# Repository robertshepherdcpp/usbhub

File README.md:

# house of wires
my fifth project for fallout!

**what is it?**
- the house of wires is a project to help remove the mess of wires! having a hub that usbs connect to creating a more organized layout
- the project is made to resemble a model house in which wires are connected and the project handles the rest (power etc.)
- the available usb options: 1 usb c power output, 3 usb a outputs (e.g. for charging your phone, charging your watch and anything else that needs charging)
- and then there is one usb input which spilts off into the other usb ports.

**how to use it?**
- print off the case and pcb (and purchase all items from the BOM)
- then to put the case on put the top half the case on the pcb (you know its the top if it has a door) and the base on the bottom, then using the 4M screws screw through. the parts of the screws pointing out the back
act as the base of the project!.
- then simply plug in a usb c port into the project (at the top)
- then connect the other usbs u need!
- just use these usbs as normal!

**how it works**
- the brain of this project is the SL2.1S, which splits the input usb into 5 channels!
- i didnt write any additional firmware for this project, that was all that was needed!

**how i made the project**
- made using kicad (for the pcb) and fusion (for the CAD design)
- using the fallout tutorial (as shown below) as a guide.

**my inspiration for the project/the why**
- i find that my desk is always messy with various wires, and i thought it would be cool to have a way to organise these (and do it in a fun way aswell!)
- i saw that there was a tutorial for a usb hub on [fallout](https://fallout.hackclub.com/docs/guided-projects/usb-hub), so i decided to give it a go (helping to improve my hardware skills!)

**screenshots:**
the schematic:

the pcb layout:

3d model:

the cad:

zine:

**the BOM**

total cost: $17.02 (not including shipping from digitkey and lcsc)

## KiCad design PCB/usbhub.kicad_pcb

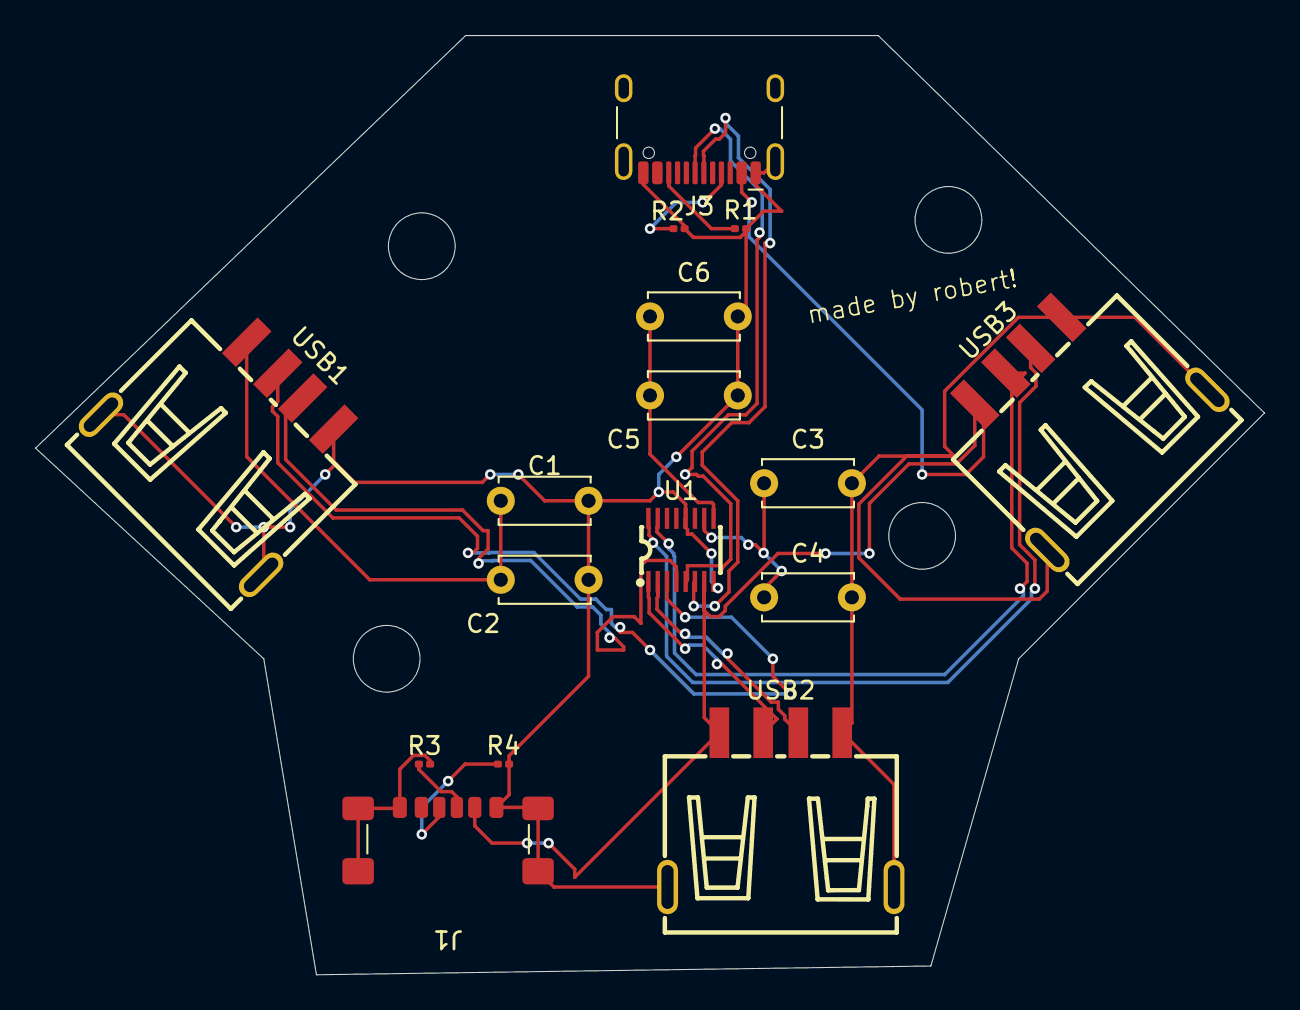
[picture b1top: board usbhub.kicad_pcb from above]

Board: 2 copper layers, 70.0 x 53.5 mm, 16 parts (0 on the bottom side), 16 nets.

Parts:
C1, C2: 1uf; C_Disc_D5.0mm_W2.5mm_P5.00mm
C3, C5: 1uF; C_Disc_D5.0mm_W2.5mm_P5.00mm
C4, C6: 100nF; C_Disc_D5.0mm_W2.5mm_P5.00mm
J1: USB_C_Receptacle_PowerOnly_6P; USB_C_Receptacle_GCT_USB4135-GF-A_6P_TopMnt_Horizontal
J3: USB_C_Receptacle_USB2.0_16P; USB_C_Receptacle_HCTL_HC-TYPE-C-16P-01A
R1, R2: 5.1kR; R_0201_0603Metric
R3, R4: 5.1k; R_0201_0603Metric
U1: SSOP-16_L4.6-W2.6-P0.53-LS4.0-BL
USB1, USB2, USB3: USB-A-TH_10.0QHHTZB6.3

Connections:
+5V: C1.1, C2.1, J1.A9 (VBUS), J1.B9 (VBUS), J3.A4 (VBUS), J3.A9 (VBUS), J3.B4 (VBUS), J3.B9 (VBUS), U1.7 (VDD5), USB1.1 (VCC), USB2.1 (VCC), USB3.1 (VCC)
DN: J3.A7 (D-), J3.B7 (D-), U1.5 (UDM)
DN1: U1.3 (DM1), USB1.2 (D-)
DN2: U1.1 (DM2), USB2.2 (D-)
DN3: U1.15 (DM3), USB3.2 (D-)
DP: J3.A6 (D+), J3.B6 (D+), U1.6 (UDP)
DP1: U1.4 (DP1), USB1.3 (D+)
DP2: U1.2 (DP2), USB2.3 (D+)
DP3: U1.16 (DP3), USB3.3 (D+)
GND: C1.2, C2.2, C3.2, C4.2, C5.2, C6.2, J1.A12 (GND), J1.B12 (GND), J1.S1 (SHIELD), J3.A1 (GND), J3.A12 (GND), J3.B1 (GND), J3.B12 (GND), J3.S1 (SHIELD), R1.2, R2.2, R3.2, R4.2, U1.8 (VSS), U1.12 (XIN), USB1.4 (GND), USB1.5, USB1.6, USB2.4 (GND), USB2.5, USB2.6, USB3.4 (GND), USB3.5, USB3.6
unnamed: J1.A5 (CC1), R4.1
unnamed: J1.B5 (CC2), R3.1
unnamed: J3.A5 (CC1), R2.1
unnamed: J3.B5 (CC2), R1.1
unnamed: C3.1, C4.1, U1.10 (VDD18)
unnamed: C5.1, C6.1, U1.9 (VDD33)

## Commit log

2026-05-02 Add BOM section to README with cost details
    Added BOM section with total cost and image.
2026-05-02 Add zine image to README
    Added an image for the zine section in the README.
2026-05-02 add the pcb files
2026-05-08 Update project inspiration section in README
2026-06-01 add updated gerber files
2026-06-01 add the new zine (just a new colour scheme)
2026-06-01 uploading the step file
2026-06-09 add the total cost row to the BOM
2026-06-09 Fix typo in column header from 'Descirption' to 'Description'
2026-06-09 Add image to BOM section in README
    Added an additional image to the BOM section.
2026-06-09 add the new zine.
2026-06-11 add the case cad step file.
2026-06-12 add the updated pcb screenshots.
2026-06-12 add the updated usb files.
2026-06-20 Add new image to zine section
    Added a new image to the zine section of the README.
